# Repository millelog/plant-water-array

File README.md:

# Plant Water Array

Distributed plant moisture monitoring system with custom ESP32 sensors, a Python backend, and a React frontend. Devices self-register via captive portal WiFi provisioning, send periodic moisture readings, and receive code updates pushed over the LAN.

**Live demo:** [plants.loganmiller.dev](https://plants.loganmiller.dev) — click **Browse as Guest** to explore the UI with sample data (read-only).

## Features

- **Real-time moisture monitoring** — ESP32 sensors report soil moisture on a configurable interval
- **Watering log** — manual logging with notes, or auto-detection from sharp moisture spikes
- **Push notifications** — alerts via [ntfy.sh](https://ntfy.sh) when plants need water or devices go offline
- **Data insights** — drying rate analysis, aggregated trends, multi-sensor comparison charts, CSV export
- **Dashboard** — sortable/filterable plant cards, weather widget, kiosk mode for wall-mounted displays
- **Push deploys** — update device firmware over LAN with `deploy.py` (atomic file swap, SHA-256 verified)
- **Captive portal provisioning** — new devices create a WiFi AP for zero-config setup
- **PWA** — installable on mobile, responsive layout with bottom navigation
- **Light/dark themes** — dark "Greenhouse Control Room" theme by default, light mode available
- **JWT authentication** — admin login with guest demo mode
- **Database maintenance** — backup downloads, configurable data retention, health stats
- **Custom PCB** — KiCad schematic and board files in `pcb/`

## Architecture

```
ESP32 sensors  ──POST readings──▶  FastAPI backend  ◀──polls──  React frontend
  (MicroPython)                     (SQLite DB)                  (Vite + Tailwind)
```

| Component | Directory | Stack |
|-----------|-----------|-------|
| Backend | `backend/` | FastAPI, SQLAlchemy, SQLite |
| Frontend | `frontend/` | React 18, TypeScript, Tailwind, Radix UI, Recharts |
| Embedded | `embeded-src/` | MicroPython on ESP32 |
| Hardware | `pcb/` | KiCad schematic + PCB |
| Deploy tool | `deploy.py` | CLI script, pushes code to devices over LAN |

## Development

### Backend
```bash
cd backend
source .venv/bin/activate
pip install -r requirements.txt
uvicorn main:app --reload --host 0.0.0.0 --port 8000
```
API docs at http://localhost:8000/docs

### Frontend
```bash
cd frontend
pnpm install
pnpm dev          # Vite dev server on port 5173
pnpm build        # TypeScript compile + Vite bundle
pnpm lint         # ESLint
```

### ESP32 Flashing
```bash
python flash_esp.py               # Auto-detect port, flash MicroPython, upload source
python flash_esp.py --sync-only   # Upload source files only
python -m mpremote connect <port> repl   # Serial console
```

### Deploying Code to Devices
```bash
python deploy.py                  # Push embeded-src/*.py to all devices over LAN
python deploy.py --dry-run        # Preview what would be deployed
python deploy.py --server URL     # Override backend URL
```

### Docker Compose
```bash
docker compose up --build         # Run backend + frontend together
```
See [docs/DEPLOYMENT.md](docs/DEPLOYMENT.md) for production deployment details.

## Data Flow

1. ESP32 boots → connects WiFi (or starts captive portal for provisioning)
2. Starts update server on port 8266 for receiving push deploys
3. Registers itself via `POST /devices/register_device`, then registers sensors via `POST /sensors/`
4. Main loop: reads moisture → `POST /readings`, heartbeat every 300s
5. Backend checks thresholds on new readings → creates alerts, sends ntfy notifications
6. Frontend polls backend APIs to display devices, readings, alerts
7. Developer runs `python deploy.py` → pushes code to all online devices, devices reboot with new code

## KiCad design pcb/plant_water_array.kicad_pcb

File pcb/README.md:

# Plant Water Array — PCB Design

Breakout board for ESP32 DevKit V1 with OLED display and 5 moisture sensor connectors.

## Board Summary

```
+--------------------------------------------------+
|                                                  |
|  [OLED 4-pin]              [ESP32 DevKit V1]    |
|   GND VCC SCL SDA           L-socket  R-socket  |
|                              (1x15)    (1x15)    |
|                                                  |
|  [J_S1] [J_S2] [J_S3] [J_S4] [J_S5]           |
|   G34    G35    G36    G39    G32               |
+--------------------------------------------------+
```

## Parts List (per board)

### PCB Connectors (solder onto the board)

| Part | Qty | Search Term | Notes |
|------|-----|-------------|-------|
| 1x15 Female Pin Socket (2.54mm) | 2 | "1x15 pin socket 2.54mm" | ESP32 DevKit mounts into these |
| 1x4 Female Pin Socket (2.54mm) | 1 | "1x4 pin socket 2.54mm" | SSD1306 OLED plugs in here |
| JST-XH 3-pin vertical header (B3B-XH-A) | 5 | "JST XH 3 pin male header vertical" | Board-side sensor connectors |

### Sensor Cable Parts (per sensor, 5 per board)

| Part | Qty | Search Term | Notes |
|------|-----|-------------|-------|
| JST-XH 3-pin plug housing (XHP-3) | 1 | "JST XH 3 pin female housing" | Mates with B3B-XH-A header |
| JST-XH crimp contacts (SXH-001T-P0.6) | 3 | "JST XH crimp terminal" | One per wire |
| 3-conductor wire (22-26 AWG) | ~1m | "3 conductor 24AWG wire" | Length as needed, up to ~2m |

### Quantities for 5 Boards

| Part | Total Qty |
|------|-----------|
| 1x15 Female Pin Socket | 10 |
| 1x4 Female Pin Socket | 5 |
| JST-XH 3-pin header (B3B-XH-A) | 25 |
| JST-XH 3-pin housing (XHP-3) | 25 |
| JST-XH crimp contacts | 75 |
| 3-conductor wire | ~25m |

### Where to Buy

- **Amazon** (fastest) — search "JST XH connector kit" (~$10-15 for assorted kit with headers + housings + crimp pins). Separately get a pack of "female pin header socket 2.54mm" (~$5-7).
- **AliExpress** (cheapest, 2-3 week shipping) — same searches, about 1/3 the price.
- **Digikey / Mouser** (exact part numbers, reliable) — B3B-XH-A ~$0.15ea, XHP-3 ~$0.10ea, SXH-001T-P0.6 ~$0.05ea, pin sockets ~$0.50ea.

A JST crimp tool (~$25) is helpful but you can solder wires directly to the crimp contacts instead.

## Pin Mapping

| Connector | Pin 1 | Pin 2 | Pin 3 | ESP32 GPIO |
|-----------|-------|-------|-------|------------|
| J_S1 | GND | 3V3 | SIG | GPIO 34 |
| J_S2 | GND | 3V3 | SIG | GPIO 35 |
| J_S3 | GND | 3V3 | SIG | GPIO 36 (VP) |
| J_S4 | GND | 3V3 | SIG | GPIO 39 (VN) |
| J_S5 | GND | 3V3 | SIG | GPIO 32 |
| J_OLED | GND | 3V3 | SCL (GPIO 22) | SDA (GPIO 21) |

## Generating the Netlist

```bash
cd pcb/
python generate_netlist.py
# Produces plant_water_array.net
# Open KiCad PCB Editor → File → Import Netlist
```

No dependencies required — just Python.

## PCB Layout Tips

- ESP32 socket headers in the center (25.4mm apart, verify with your DevKit)
- OLED header on top edge
- JST-XH connectors along bottom or side edge
- Keep traces wide (0.5mm+)
- Pour a ground plane on the back copper layer (select B.Cu → Place → Add Filled Zone → net GND)

## Ordering PCBs (JLCPCB)

1. Export Gerbers from KiCad: **File → Fabrication Outputs → Gerbers**, then **Generate Drill Files**
2. Zip the `gerber_out/` folder
3. Go to **jlcpcb.com** → **Order Now** → upload the zip

### JLCPCB Settings

| Setting | Value |
|---------|-------|
| Base Material | FR-4 |
| Layers | 2 |
| PCB Qty | 5 |
| PCB Thickness | 1.6mm |
| PCB Color | Green (cheapest) |
| Surface Finish | HASL (or LeadFree HASL) |
| Copper Weight | 1 oz |
| Everything else | Default |

Cost: ~$2-5 + shipping ($1-5 standard, ~$15-20 DHL express).

## Sensor Cable Assembly

Each sensor cable is a 3-wire bundle with a JST-XH plug on the board end:

```
Sensor                Board End
┌─────────┐         ┌──────────┐
│ S (sig) │─────────│ Pin 3    │
│ + (VCC) │─────────│ Pin 2    │
│ - (GND) │─────────│ Pin 1    │
└─────────┘         └──────────┘
                    JST-XH plug
```

Use 3-conductor cable (ribbon cable or twisted triple) — can run 1-2 meters without issues for analog signals.

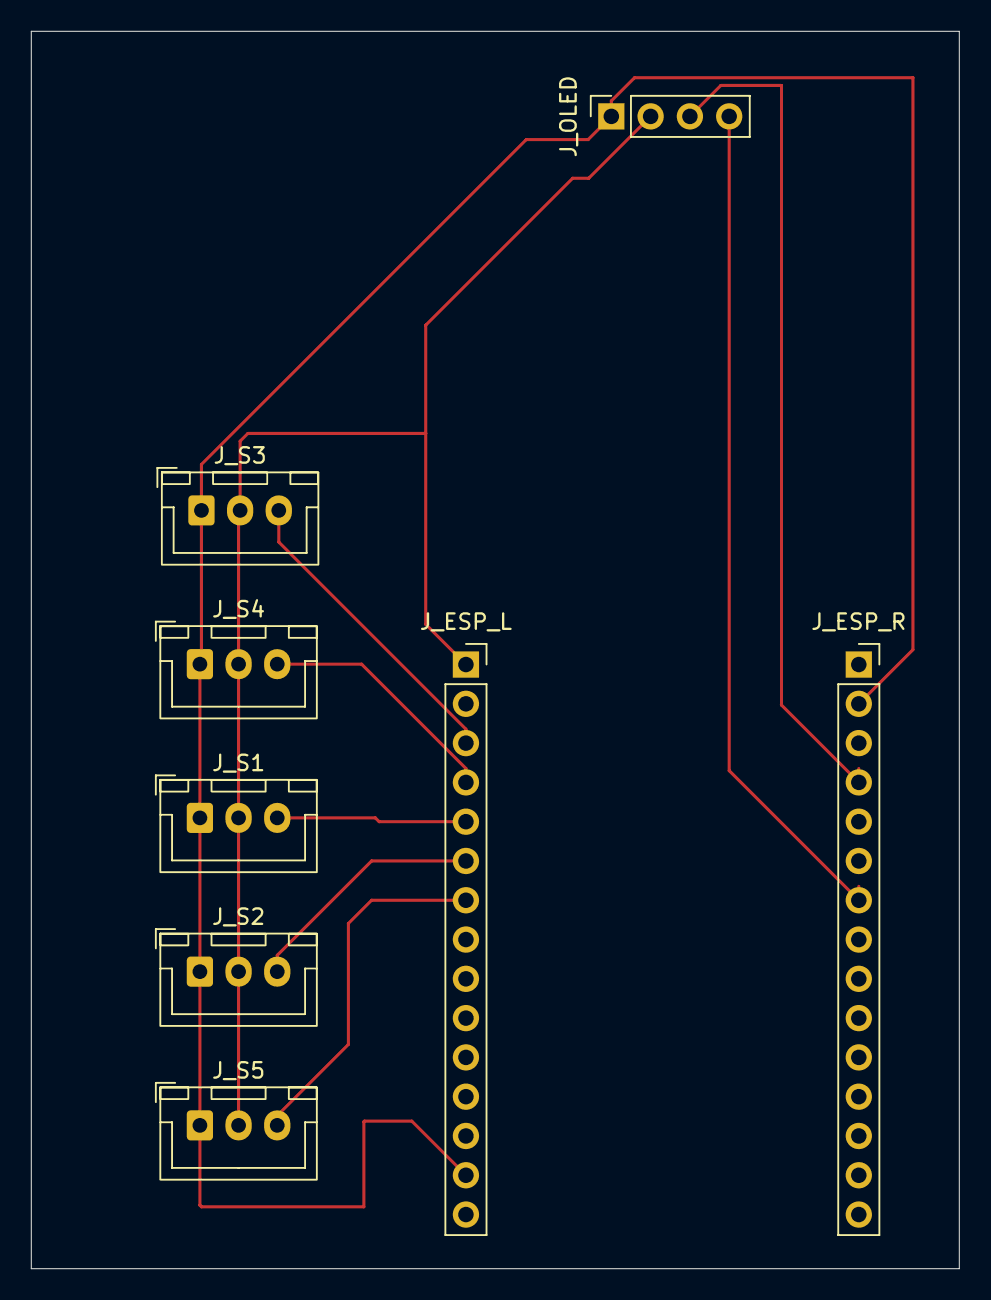
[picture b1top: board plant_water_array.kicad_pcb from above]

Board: 2 copper layers, 60.0 x 80.0 mm, 8 parts (0 on the bottom side), 9 nets.

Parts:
J_ESP_L: ESP32_Left; PinSocket_1x15_P2.54mm_Vertical
J_ESP_R: ESP32_Right; PinSocket_1x15_P2.54mm_Vertical
J_OLED: SSD1306_OLED; PinSocket_1x04_P2.54mm_Vertical
J_S1: Moisture_G34; JST_XH_B3B-XH-A_1x03_P2.50mm_Vertical
J_S2: Moisture_G35; JST_XH_B3B-XH-A_1x03_P2.50mm_Vertical
J_S3: Moisture_G36; JST_XH_B3B-XH-A_1x03_P2.50mm_Vertical
J_S4: Moisture_G39; JST_XH_B3B-XH-A_1x03_P2.50mm_Vertical
J_S5: Moisture_G32; JST_XH_B3B-XH-A_1x03_P2.50mm_Vertical

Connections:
+3V3: J_ESP_L.1, J_OLED.2, J_S1.2, J_S2.2, J_S3.2, J_S4.2, J_S5.2
GND: J_ESP_L.14, J_ESP_R.2, J_OLED.1, J_S1.1, J_S2.1, J_S3.1, J_S4.1, J_S5.1
I2C_SCL: J_ESP_R.4, J_OLED.3
I2C_SDA: J_ESP_R.7, J_OLED.4
SENSOR1_G34: J_ESP_L.5, J_S1.3
SENSOR2_G35: J_ESP_L.6, J_S2.3
SENSOR3_G36: J_ESP_L.3, J_S3.3
SENSOR4_G39: J_ESP_L.4, J_S4.3
SENSOR5_G32: J_ESP_L.7, J_S5.3

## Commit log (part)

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2024-09-20 Init commit
2024-09-20 Rearranging project structure to fix imports
2024-09-20 Refactor to only include sensor reading side for now
2024-09-20 Adds the frontend
2024-09-20 Fixes tailwind config and cors
2024-09-20 Embedded device adoption updated
2024-09-21 Readings posting to DB from ESP32
2024-09-23 Initial changes for new dashboard
2024-09-25 Graph readings working
2024-09-25 fixes timestamps in data table
2024-09-30 Gets readings working
2024-10-14 Refactor secrets into config.py
2026-03-09 Adds feature list
2026-03-10 Update example config with a generated DEPLOY_TOKEN for enhanced security
2026-03-10 Update API endpoint paths to ensure consistent trailing slashes
